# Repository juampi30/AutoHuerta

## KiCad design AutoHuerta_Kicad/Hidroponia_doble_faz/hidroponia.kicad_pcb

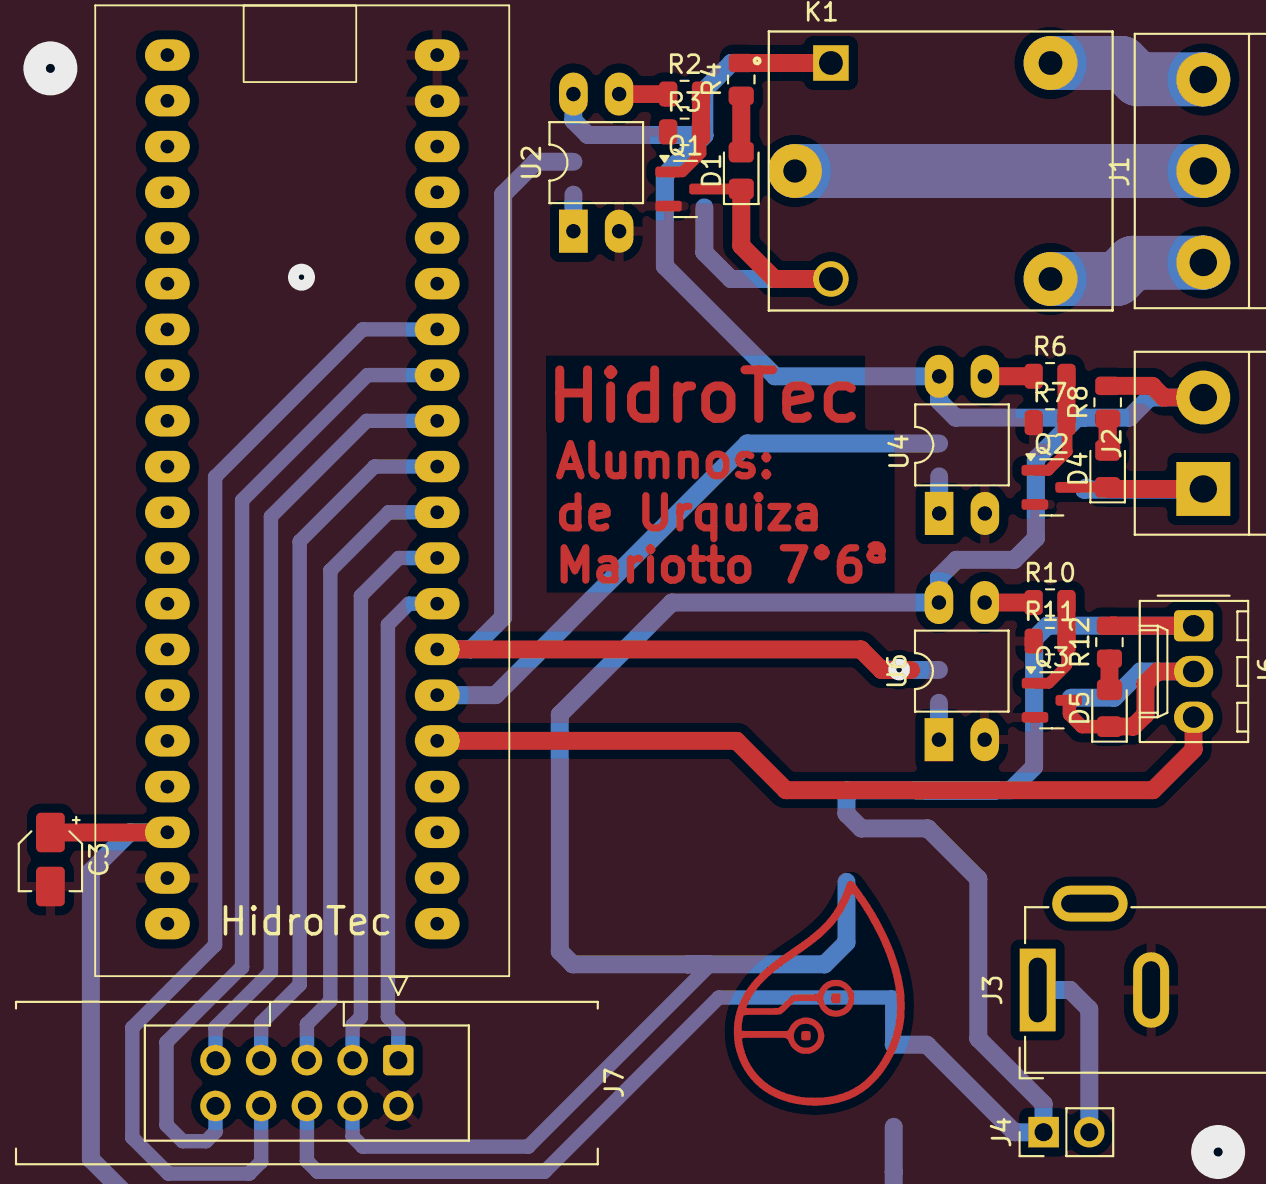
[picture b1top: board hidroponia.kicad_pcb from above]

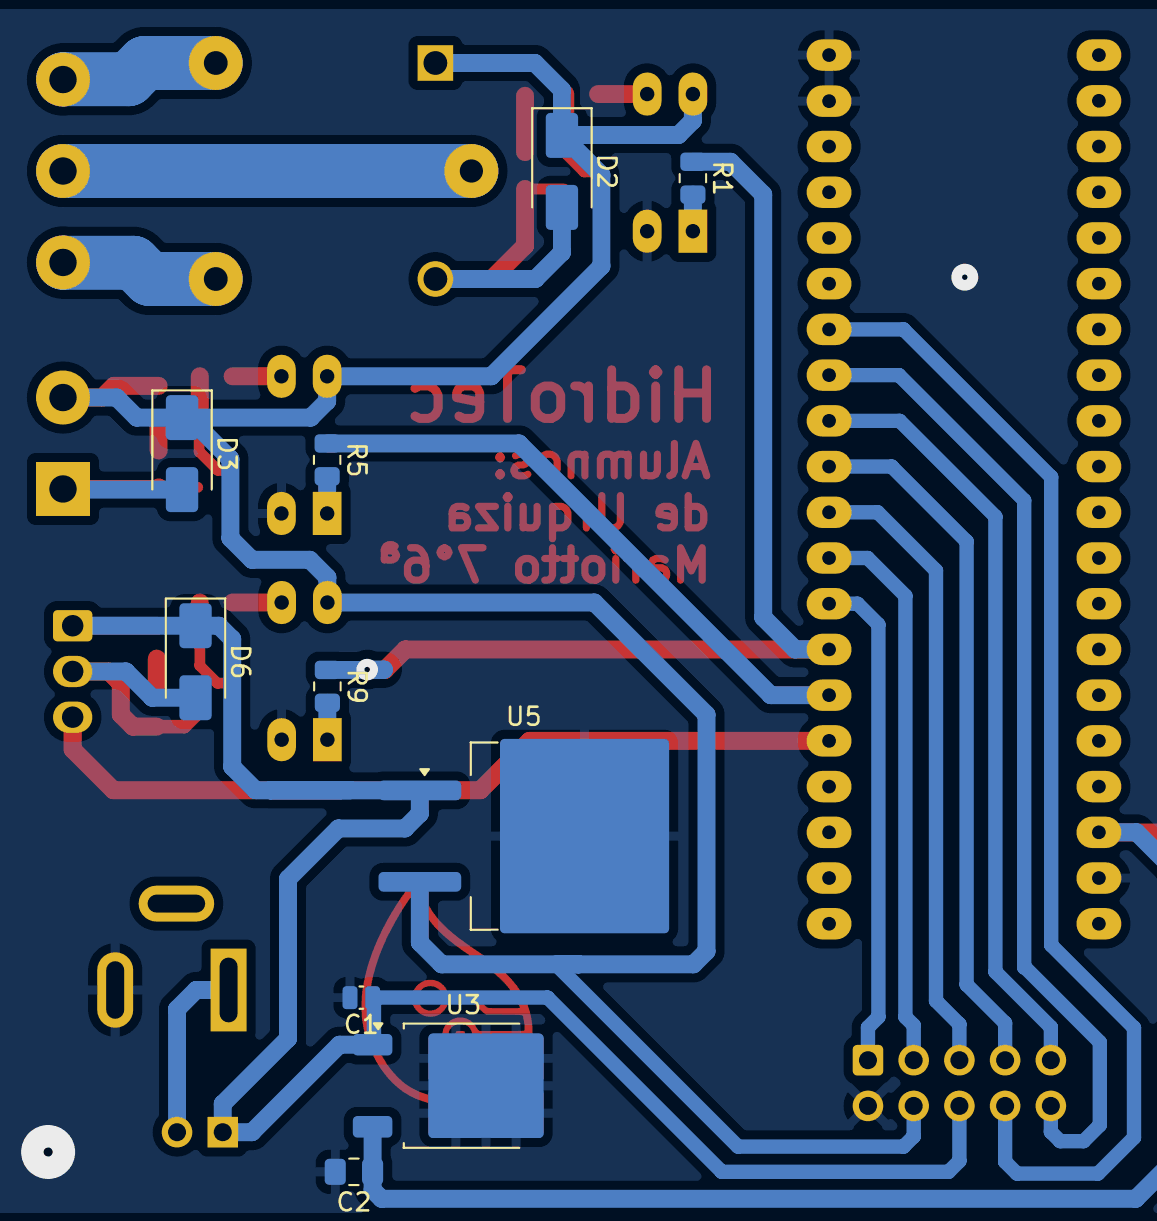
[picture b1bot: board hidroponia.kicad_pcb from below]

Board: 2 copper layers, 37 parts (10 on the bottom side), 33 nets.

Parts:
C1: 0,33uf; C_0504_1310Metric_Pad0.83x1.28mm_HandSolder
C2: 0,1uf; C_0805_2012Metric_Pad1.18x1.45mm_HandSolder
C3: 0,1uf; CP_Elec_3x5.4
D1, D4, D5: LED; LED_0805_2012Metric_Pad1.15x1.40mm_HandSolder
D2, D3, D6: 1N4007; D_SMA
J1: bornera; TerminalBlock_bornier-3_P5.08mm
J2: bornera; TerminalBlock_bornier-2_P5.08mm
J3: Barrel_Jack; BarrelJack_GCT_DCJ200-10-A_Horizontal
J4: pin; PinHeader_1x02_P2.54mm_Vertical
J6: Pin; Molex_KK-254_AE-6410-03A_1x03_P2.54mm_Vertical
J7: Pin; IDC-Header_2x05-1MP_P2.54mm_Latch6.5mm_Vertical
K1: RELAY; RELAY_SRD-05VDC-SL-C
Q1, Q3: BC817; SOT-23
Q2: BS170F; SOT-23
R1, R4, R5, R6, R8, R9: 330Ω; R_0805_2012Metric
R2, R10, R12: 1kΩ; R_0805_2012Metric
R3, R7, R11: 10kΩ; R_0805_2012Metric
U1: stm32
U2, U4, U6: PC817; DIP-4_W7.62mm_LongPads
U3: L7805; TO-252-2
U5: L7805; TO-263-2_TabPin1

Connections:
+5V: D2.1 (K), D3.1 (K), J2.2, J7.4, K1.A1, R4.2, R8.2, U2.4, U4.4, U5.2 (GND), U6.4
+5V1: C2.1, C3.1, U1.18 (5V), U3.3 (OUT)
+12V: C1.1, D6.1 (K), J4.1, J6.1, J7.6, R12.2, U3.1 (IN), U5.1 (IN)
A3: J7.1, U1.28 (A3)
A4: J7.3, U1.29 (A4)
A5: J7.5, U1.30 (A5)
A6: J7.7, U1.31 (A6)
A7: J7.9, U1.32 (A7)
B0: J7.10, U1.33 (B0)
B1: J7.8, U1.34 (B1)
BOMBA: R5.1, U1.26 (A1)
COM1: J1.2, K1.COM
GND: C1.2, C2.2, C3.2, J3.2, J7.2, Q1.2 (E), Q2.2 (S), Q3.2 (E), R3.1, R7.1, R11.1, U1.19 (GND), U1.39 (GND), U1.40 (GND), U2.2, U3.2 (GND), U4.2, U5.1 (IN), U6.2
LED & FAN: R1.1, R9.1, U1.27 (A2)
NC1: J1.3, K1.NC
NO1: J1.1, K1.NO
unnamed: D1.2 (A), R4.1
unnamed: D1.1 (K), D2.2 (A), K1.A2, Q1.3 (C)
unnamed: D3.2 (A), D4.1 (K), J2.1, Q2.3 (D)
unnamed: D4.2 (A), R8.1
unnamed: D5.2 (A), R12.1
unnamed: D5.1 (K), D6.2 (A), J6.2, Q3.3 (C)
unnamed: J3.1, J4.2
unnamed: Q1.1 (B), R2.2, R3.2
unnamed: Q2.1 (G), R6.2, R7.2
unnamed: Q3.1 (B), R10.2, R11.2
unnamed: R1.2, U2.1
unnamed: R2.1, U2.3
unnamed: R5.2, U4.1
unnamed: R6.1, U4.3
unnamed: R9.2, U6.1
unnamed: R10.1, U6.3
VEL: J6.3, U1.25 (A0)

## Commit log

2026-04-08 Create AutoHueta.gan
    Diagrama de Gantt
2026-04-15 AutoHuerta
    Añadi la carpeta AutoHuerta de kicad
2026-04-15 Agregue carpetas
    Ideas de logos para HidroTec
2026-04-15 Actualizacion de placa
    agregamos la entrada de 12v, agregamos el control para el motor, tambien pusimos huellas.
2026-04-17 Actualizacion de plaqueta 17/4
    agregue el control del ventilador, agregue capacito para stm32, puse huellas faltantes y conecte los pines del stm32
2026-04-22 Actualizacion de placa
    Agregamos pinera de 8 pines y tambien agregamos control de velocidad para el ventilador.
2026-04-22 Añadí el Logo
    Ordene carpetas y puse el logo en simbolo y huella
2026-04-22 Esquematico terminado
    Terminamos de corregir y agregar cosas al esquematico y empezamos a acomodar los componentes en el pcb
2026-04-24 PCB
    Acomodamos un poco el PCB y cambiamos pines de lugar
2026-04-29 PCB
    PCB casi terminado, y cambiamos unas cosas del esquematico
2026-05-06 commit d vuelta
2026-05-06 prueba fin
    quilombo areglado
2026-05-06 PCB
    cambios en el pcb
2026-05-17 PCB actualizado
    faltan enrutar 5 pistas
2026-05-20 actualizacion de PCB
    pruebas
2026-06-03 pcb doble faz casi listo
    pcb casi terminado
2026-06-05 PCB TERMINADO
    Terminamos el PCB
2026-06-16 gantt actualizado
